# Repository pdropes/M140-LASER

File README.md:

# 2W LASER - M140 Nichia

Construction of a driver for this small diode, power by 18650 battery.
- Max output = 4.8V 2A
- 4 Selectable power levels (0.1-0.5-1.0-1.5A)
- Constant CC with soft start
- Battery monitoring in charge and discharge

Firmware: Bascom AVR 2.0.8.1; Layout: CadSoft EAGLE 6.5.0

*Stay creative (& always wear safety glasses)

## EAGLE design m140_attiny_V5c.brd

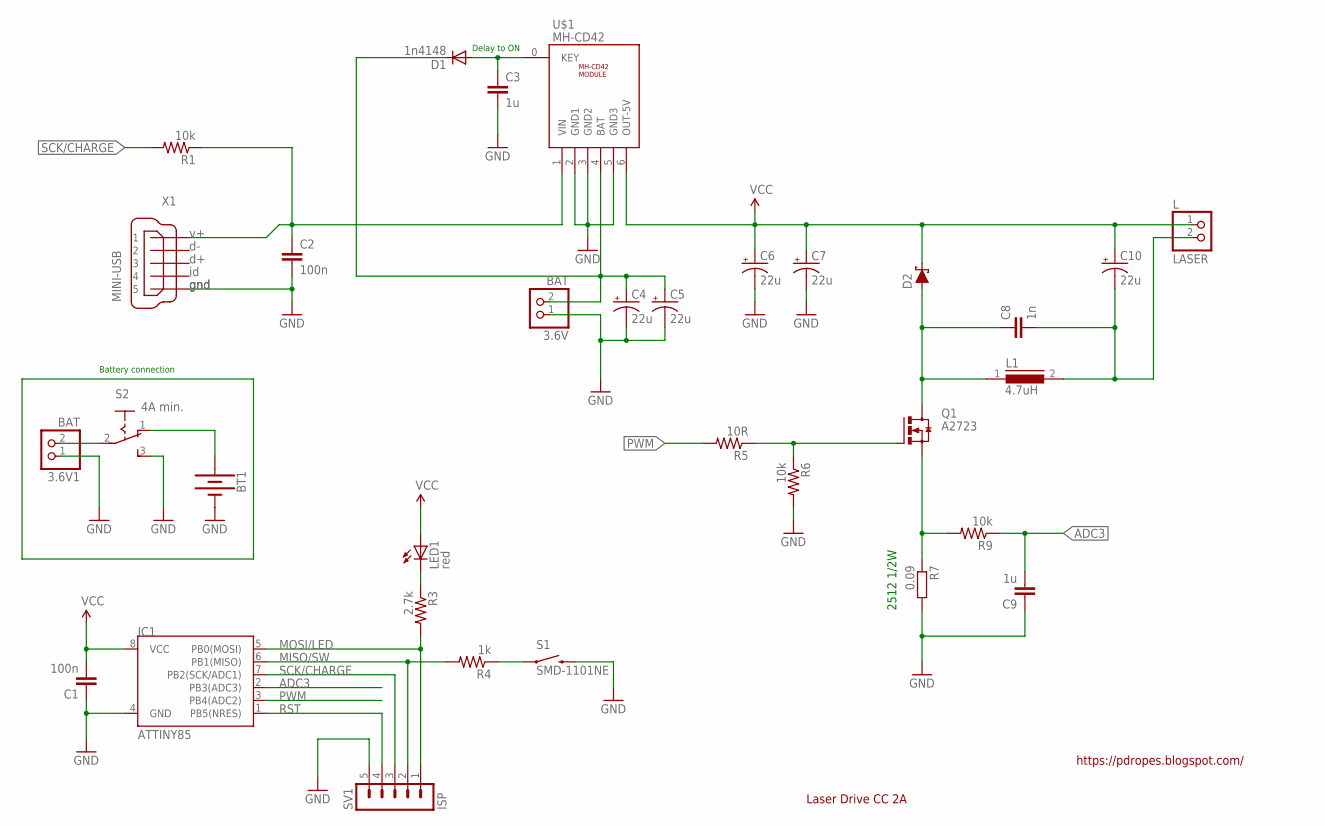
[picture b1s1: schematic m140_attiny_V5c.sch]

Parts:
3.6V, 3.6V1: BAT; 1X02
BT1: BATTERY-18650; BATTERY_18650-HOLDER
C1, C2: 100n; 0805
C3, C9: 1u; 0805
C4, C5, C6, C7, C10: 22u; EIA3216-KIT
C8: 1n; 0805
D1: 1n4148; MICROMELF-R
D2: 3A/40V/500mV; SMA-DIODE
IC1: ATTINY85; SO08-EIAJ
L: LASER; 1X02
L1: 4.7uH; DR74
LED1: red; CHIPLED_0805
Q1: A2723; SOP-ADVANCE
R1, R6, R9: 10k; 0805
R3: 2.7k; 0805
R4: 1k; 0805
R5: 10R; 0805
R7: 0.09; R2512
S1: SMD-1101NE; TACTILE-SWITCH-1101NE
S2: 4A min.; 255SB
SV1: ISP; MA05-1
U$1: MH-CD42
X1: MINI-USB; 32005-301

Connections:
ADC3: C9.2, IC1.2 (PB3(ADC3)), R9.1
B+: 3.6V.2, C4.A (+), C5.A (+), D1.C, U$1.4 (BAT)
GND: 3.6V.1, 3.6V1.1, BT1.GND@1 (-), C1.1, C2.2, C3.2, C4.C (-), C5.C (-), C6.C (-), C7.C (-), C9.1, IC1.4 (GND), R6.2, R7.2, S1.P$2 (2), S2.3 (S), SV1.5, U$1.2 (GND1), U$1.3 (GND2), U$1.5 (GND3), X1.5
KEY: C3.1, D1.A, U$1.0 (KEY)
L-: C8.2, C10.C (-), L.2, L1.2
MISO/SW: IC1.6 (PB1(MISO)), R4.2, SV1.2
MOSI/LED: IC1.5 (PB0(MOSI)), R3.2, SV1.1
unnamed: BT1.PWR@1 (+), S2.1 (O)
unnamed: R4.1, S1.P$1 (1)
unnamed: 3.6V1.2, S2.2
unnamed: LED1.C, R3.1
PWM: IC1.3 (PB4(ADC2)), R5.2
Q1D: C8.1, D2.A, L1.1, Q1.5 (D), Q1.6 (D), Q1.7 (D), Q1.8 (D), Q1.TH (D)
Q1G: Q1.4 (G), R5.1, R6.1
Q1S: Q1.1 (S), Q1.2 (S), Q1.3 (S), R7.1, R9.2
RST: IC1.1 (PB5(NRES)), SV1.4
SCK/CHARGE: IC1.7 (PB2(SCK/ADC1)), R1.2, SV1.3
USB+: C2.1, R1.1, U$1.1 (VIN), X1.1
VCC: C1.2, C6.A (+), C7.A (+), C10.A (+), D2.C, IC1.8 (VCC), L.1, LED1.A, U$1.6 (OUT-5V)

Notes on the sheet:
Laser Drive CC 2A
gnd
Delay to ON
2512 1/2W
Battery connection
https://pdropes.blogspot.com/

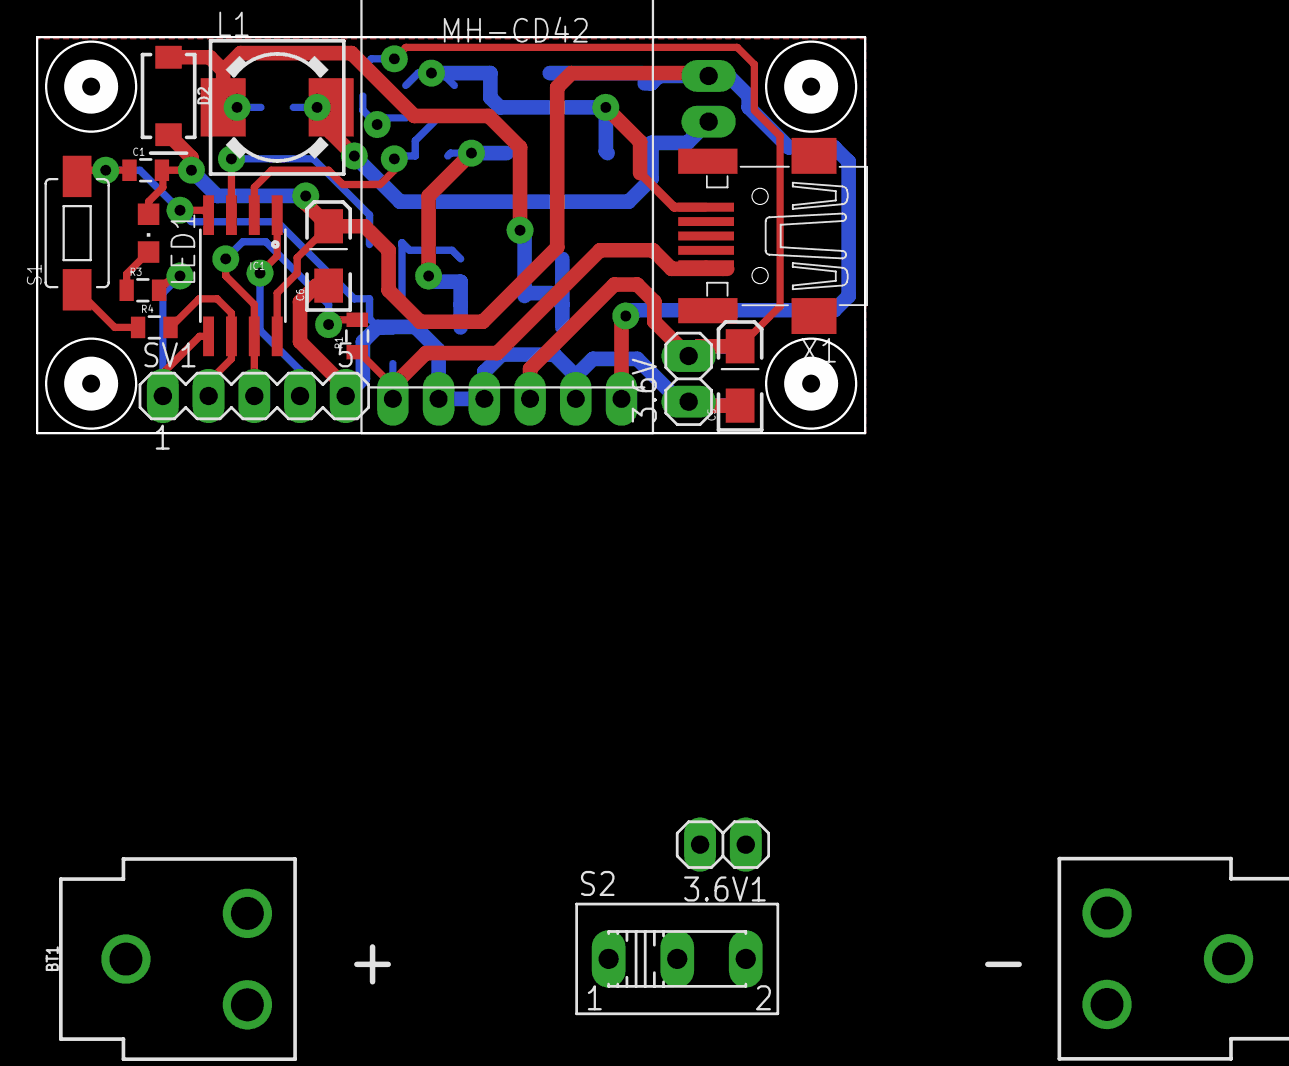
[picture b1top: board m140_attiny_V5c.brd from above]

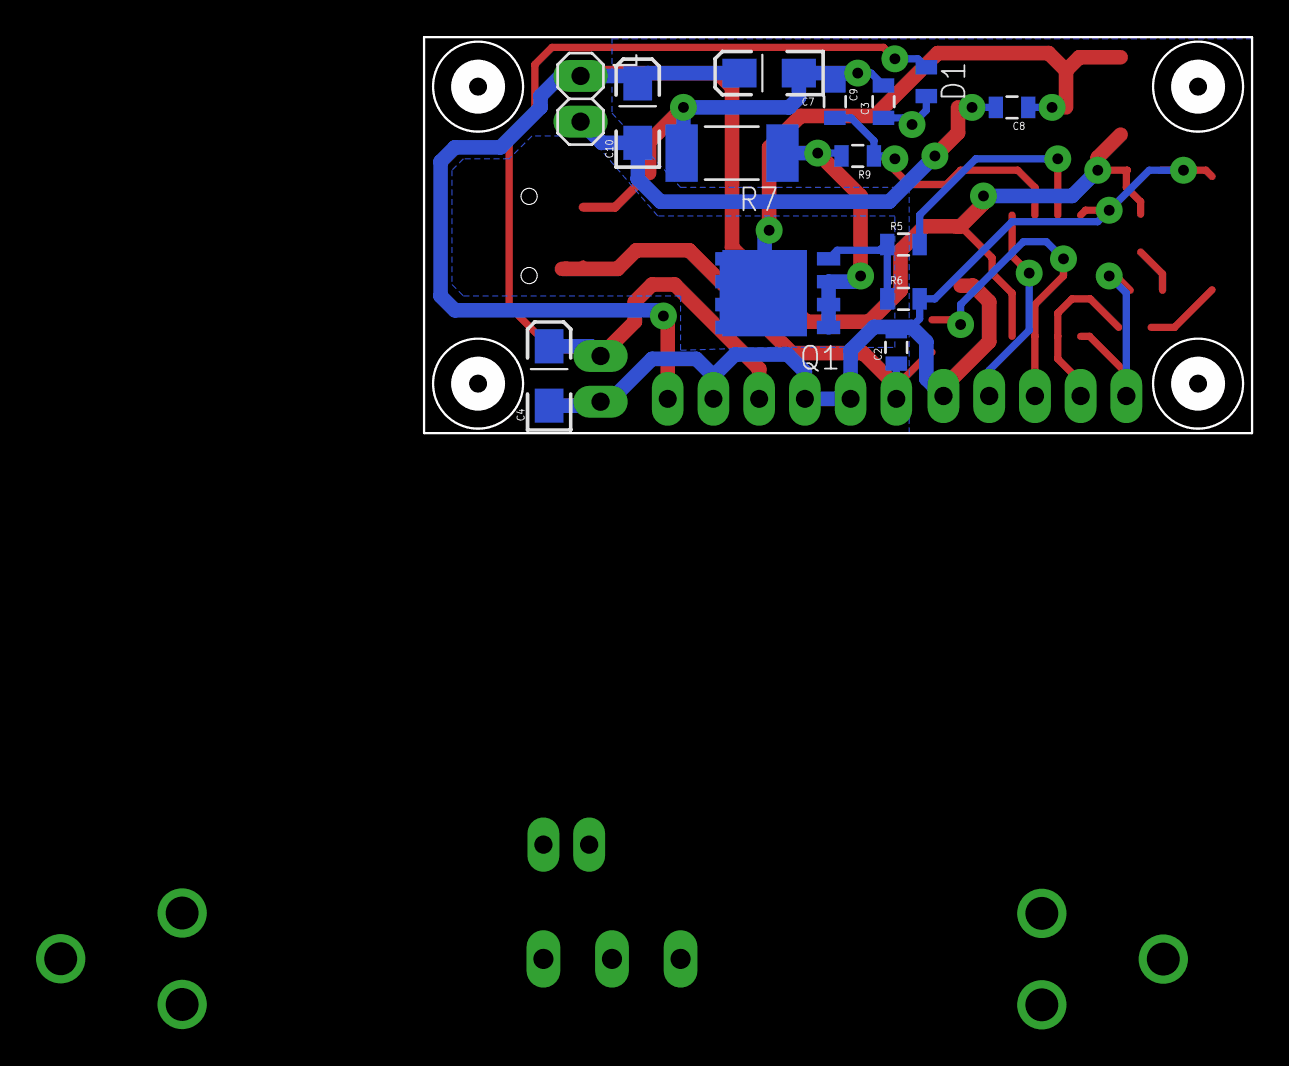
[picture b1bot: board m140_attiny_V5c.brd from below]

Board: 2 copper layers, 46.0 x 22.0 mm, 33 parts (14 on the bottom side), 19 nets.

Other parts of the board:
U$2: LASER_HEAT_SINK

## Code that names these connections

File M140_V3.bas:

'04-05-2022
'FUSES: E:FF H:DF L:E1

'Pinout ATtiny85:
'1- PB5 (PCINT5 / Reset / ADC0 / DW)
'2- PB3 (PCINT3/XTAL1/CLKI/OC1B/ADC3)
'3- PB4 (PCINT4/XTAL2/CLKO/_OC1B/ADC2)
'4- GND
'5- PB0 (MOSI/DI/SDA/AIN0/OC0A/_OC1A/AREF/PCINT0)
'6- PB1 (MISO/DO/AIN1/OC0B/OC1A/PCINT1)
'7- PB2 (SCK/USCK/SCL/ADC1/T0/INT0/PCINT2)
'8- VCC

'PB0 = SWITCH
'PB1 = LED
'PB2 = USB_charger
'PB3 = ADC3
'PB4 = PWM


$regfile = "attiny85.dat"
$crystal = 16000000
'$hwstack = 32
'$swstack = 10
'$framesize = 40

Dim Value As Word
Dim Ilaser As Word
Dim Cnt , Cnt2 As Word
Dim Pwm_value As Byte

Dim Pselect(4) As Byte                                      'Bascom não aceita arrays de constantes :/

'RSense =0.09ohms
'ADC Ref=1.1V
'Current=1.1V/0.09ohms =12.2(2)A
'LSb=12.2(2)/1024=0.011936V
'0.1A=0.1/ 0.011936V = ~8,4
'0.5A=0.5/ 0.011936V = ~41,9
'1.0A=1.0/ 0.011936V = ~83,8
'1.5A=1.5/ 0.011936V = ~125,7
Pselect(1) = 9 : Pselect(2) = 42 : Pselect(3) = 84 : Pselect(4) = 126       '0.1/0.5/1.0/1.5A


Dim Power_position , Power_output As Word                   'Tem de ser word Power_output

Config Adc = Single , Prescaler = 4 , Reference = Internal_1.1

Const Adc_ilaser = 3

Switch Alias Pinb.0
Led Alias Portb.1
Charger Alias Pinb.2

Config Charger = Input
Charger = 0
Config Led = Output
Led = 1
Config Switch = Input
Switch = 1

Declare Function Get_adc(byval Channel As Byte) As Word
Declare Sub Pwm(_get As Word , _wanted As Word)

'-----------------------------PLL AS CLOCK SOURCE for 16MHz-------------------------
Pllcsr.plle = 1
While Pllcsr.plock = 0
Wend
Pllcsr.pcke = 1
!Ldi R24 , 110
!Out Osccal , R24

'----------------------------TIMER 1 PWM
'TCCR1  Timer/Counter1 Control Register
'CTC1 PWM1A COM1A1 COM1A0 CS13 CS12 CS11 CS10
Tccr1 = Bits(cs11 , Cs10 )
'GTCCR  General Timer/Counter1 Control Register
'TSM PWM1B COM1B1 COM1B0 FOC1B FOC1A PSR1 PSR0
Gtccr = Bits(pwm1b , Com1b1)
'TCNT1  Timer/Counter1
Tcnt1 = &H00
Ocr1a = &H00
Ocr1b = &H00                                                'PWM VALUE
Ocr1c = &HFF
Config Portb.4 = Output

'Config Portb.1 = Output
'Open "comb.1:4800,8,n,1" For Output As #1

'------------------------------------------MAIN--------------------------------------------

Enable Interrupts

Power_position = 0
Power_output = Pselect(1)
Pwm_value = 0
Led = 0
Waitms 500
Led = 1

Do
    'Espera que o switch seja activado, pisca a cada segundo
    While Switch = 1

        'Verifica se o carregador está ligado
        While Charger = 1
            Led = 0
            For Cnt = 0 To 100
                If Charger = 0 Then Cnt = 100
                Waitms 5
            Next Cnt
            Led = 1
            For Cnt = 0 To 100
                If Charger = 0 Then Cnt = 100
                Waitms 5
            Next Cnt
        Wend

        For Cnt = 0 To 250
            If Switch = 0 Then Cnt = 250
            Waitms 4
        Next Cnt
        Led = 0
        Waitms 5
        Led = 1
    Wend

    'Se passado 150ms o switch continuar activado, então habilita o laser
    Waitms 150

    Led = 0
    While Switch = 0
        Ilaser = Get_adc(adc_ilaser)
        Call Pwm(ilaser , Power_output)
        Waitms 3                                            'soft start
    Wend
    Led = 1

    'Espera um possível 2º click para alterar a potência
    If Ocr1b = 0 Then
        For Cnt = 0 To 150
            Waitms 1
            If Switch = 0 Then
                Bitwait Switch , Set
                Incr Power_position
                Power_position = Power_position And &B11    '0..3
                Power_output = Pselect(power_position + 1)  'Arrays começam em 1
             'Apresenta a potência
                Waitms 500
                For Cnt2 = 0 To Power_position
                    Led = 0
                    Waitms 100
                    Led = 1
                    Waitms 200
                Next Cnt2
                Cnt = 150
            End If
        Next Cnt
    End If


    Ocr1b = 0                                               'desliga o pwm
    Pwm_value = 0
    Waitms 200
Loop

'---------------------------------------ADC-----------------------------------------------
Function Get_adc(byval Channel As Byte) As Word
    Dim Multi_sample As Byte
    Dim Adc_value As Word

    Adc_value = 0
    For Multi_sample = 0 To 49
        Adc_value = Adc_value + Getadc(channel)
    Next Multi_sample
    Adc_value = Adc_value / 50
    Get_adc = Adc_value
End Function

'-------------------------------------TUNE PWM------------------------------------------
Sub Pwm(_get As Word , _wanted As Word)
    If _get < _wanted And Pwm_value < 200 Then
        Incr Pwm_value
        Ocr1b = Pwm_value
    End If
    If _get > _wanted And Pwm_value > 0 Then
        Decr Pwm_value
        Ocr1b = Pwm_value
    End If
End Sub

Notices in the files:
parts and their libraries:
SparkFun: Licensing: CC v3.0 Share-Alike You are welcome to use this library for commercial purposes.
SparkFun-DiscreteSemi: Licensing: Creative Commons ShareAlike 4.0 International - https://creativecommons.org/licenses/by-sa/4.0
